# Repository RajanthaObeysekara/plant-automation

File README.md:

# Plant Automation

A cloud-hosted misting/feeding controller for Dendrobium orchid greenhouses
in Sri Lanka. The addressable hardware is **not per-bench** — each farm has
one shared water tank + fertilizer mixing rig, and each greenhouse room has
one shared environment sensor + misting controller. Benches are just named,
positioned spots on a room's floor-plan map. See
[plant-automation-architecture.html](plant-automation-architecture.html)
for the fuller design writeup (some of it predates this room/farm-level
model — the tables below are current).

**New to this repo, or picking it up on a different machine?** Start with
[PROJECT.md](PROJECT.md) for setup and hardware background, but note it
also predates the room/farm re-architecture described here.

## The device model

| Level | What it owns | Addressable? |
|---|---|---|
| **Farm** (🏡) | One shared water tank (low/full sensors) + one fertigation rig (mix → stir → filter → dose). Services whichever room's feed day it is, one room at a time. | Yes — its own `device_key`, polls `/api/device/farm/*` |
| **Room** (🏠, a greenhouse) | One environment sensor (humidity/temp/rain) + misting for every bench in it, together. | Yes — its own `device_key`, polls `/api/device/room/*` |
| **Bench** | A name + a position on the room's map. No sensor, no schedule, no device of its own. | No — plain CRUD via `/api/benches` |

## Parts of this repo

| Path | What it is |
|---|---|
| `backend/` | Node/Express + Postgres + Socket.IO API. Two device-facing route groups (`/api/device/room`, `/api/device/farm`), plus REST + WebSocket for the web app. |
| `frontend/` | React dashboard — farms/rooms, live status, schedules, variety templates, draggable bench floor-plan, history. |
| `simulator/` | A single Node process that plays every room + farm controller in the fleet as live simulated hardware (mist/fertigation/tank state machines), for testing without real hardware. Sensor baselines track real current weather per farm. |
| `firmware/esp32-unit/` | Real ESP32 firmware reference — written for the older per-bench protocol; not yet updated for the room/farm split. |
| `db/init.sql` | Schema, applied automatically on first Postgres start. |

## Run it locally

```bash
cp .env.example .env      # edit if you want different local credentials
docker compose up -d --build
```

- Web app: http://localhost:8090 (default login `admin@example.com` /
  `changeme`, from `.env` — change it before this goes anywhere near
  Railway)
- Backend API directly: http://localhost:4000
- The `simulator` service auto-discovers every farm/room in the database and
  starts polling within seconds — no hardware required to see the whole
  system working.

## Protocols, on purpose

- **Device ↔ backend**: plain REST over HTTP(S), polled on an interval,
  bearer device-key auth (one key per room, one per farm). No broker to
  run, resilient to reconnects — a room keeps misting on its last-synced
  config even if this link is down.
- **Browser ↔ backend**: REST for actions/config, WebSocket (Socket.IO)
  for live push (telemetry, mist/fertigation status) so the dashboard
  doesn't have to poll.
- **User auth**: JWT. **Device auth**: a per-device random key, checked
  with a constant-time comparison against every key on file (cached
  in-memory, refreshed every 20s — see `backend/src/deviceAuth.js`).

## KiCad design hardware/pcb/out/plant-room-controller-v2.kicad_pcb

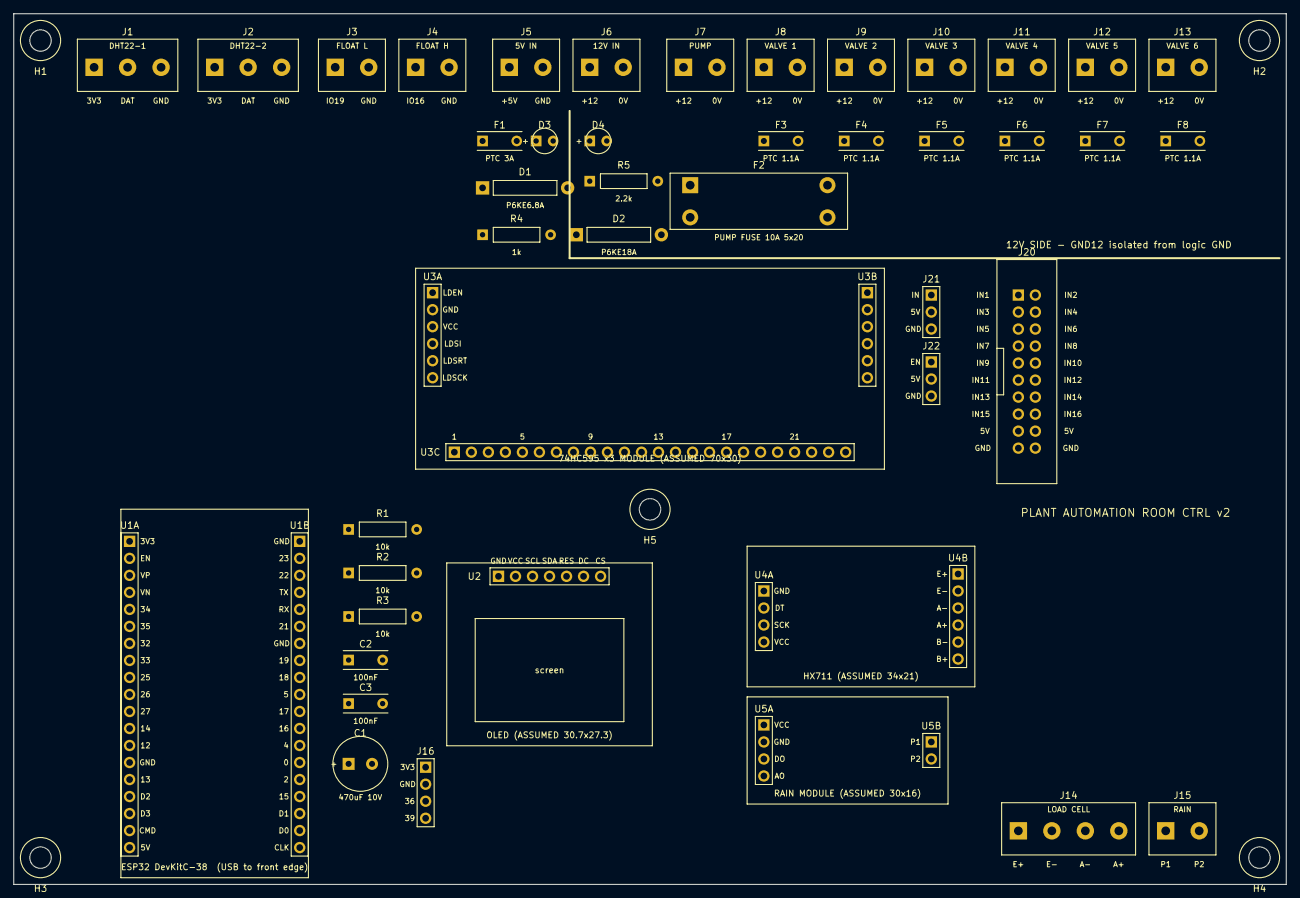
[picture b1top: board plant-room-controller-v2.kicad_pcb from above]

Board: 2 copper layers, 190.0 x 130.0 mm, 54 parts (0 on the bottom side), 58 nets, no tracks yet.

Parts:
C1: 470uF 10V; CP_Radial_D8.0mm_P3.50mm
C2, C3: 100nF; C_Disc_P5.08mm
D1: P6KE6.8A; D_DO-15_P12.70mm
D2: P6KE18A; D_DO-15_P12.70mm
D3: LED 5V; LED_D3.0mm
D4: LED 12V; LED_D3.0mm
F1: PTC 3A; Fuse_PTC_Radial_P5.10mm
F2: PUMP FUSE 10A 5x20; Fuseholder_Clip-5x20mm_P20.50x4.80mm
F3, F4, F5, F6, F7, F8: PTC 1.1A; Fuse_PTC_Radial_P5.10mm
H1, H2, H3, H4, H5: M3; MountingHole_3.2mm_M3
J1: DHT22-1; TerminalBlock_1x03_P5.00mm
J2: DHT22-2; TerminalBlock_1x03_P5.00mm
J3: FLOAT L; TerminalBlock_1x02_P5.00mm
J4: FLOAT H; TerminalBlock_1x02_P5.00mm
J5: 5V IN; TerminalBlock_1x02_P5.00mm
J6: 12V IN; TerminalBlock_1x02_P5.00mm
J7: PUMP; TerminalBlock_1x02_P5.00mm
J8: VALVE 1; TerminalBlock_1x02_P5.00mm
J9: VALVE 2; TerminalBlock_1x02_P5.00mm
J10: VALVE 3; TerminalBlock_1x02_P5.00mm
J11: VALVE 4; TerminalBlock_1x02_P5.00mm
J12: VALVE 5; TerminalBlock_1x02_P5.00mm
J13: VALVE 6; TerminalBlock_1x02_P5.00mm
J14: LOAD CELL; TerminalBlock_1x04_P5.00mm
J15: RAIN; TerminalBlock_1x02_P5.00mm
J16: SPARE IN; PinHeader_1x04_P2.54mm
J20: RELAY BOARD 2x10; IDC_BoxHeader_2x10_P2.54mm
J21: RELAY 17; PinHeader_1x03_P2.54mm
J22: RELAY PWR EN; PinHeader_1x03_P2.54mm
R1, R2, R3: 10k; R_Axial_P10.16mm
R4: 1k; R_Axial_P10.16mm
R5: 2.2k; R_Axial_P10.16mm
U1A, U1B: ESP32 socket 1x19; PinSocket_1x19_P2.54mm
U2: OLED DM0054; PinSocket_1x07_P2.54mm
U3A: 595 IN; PinSocket_1x06_P2.54mm
U3B: 595 CASCADE (NC); PinSocket_1x06_P2.54mm
U3C: 595 OUTPUTS (1-17 USED); PinSocket_1x24_P2.54mm
U4A: HX711 LOGIC; PinSocket_1x04_P2.54mm
U4B: HX711 BRIDGE; PinSocket_1x06_P2.54mm
U5A: RAIN LOGIC; PinSocket_1x04_P2.54mm
U5B: RAIN PLATE; PinSocket_1x02_P2.54mm

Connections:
5V_IN: F1.1, J5.1
+3V3: C2.1, J1.1, J2.1, J16.1, R1.2, R2.2, R3.2, U1A.1, U2.2, U3A.3, U4A.4, U5A.1
+5V: C1.1, C3.1, D1.1, D3.1, F1.2, J20.17, J20.18, J21.2, J22.2, U1A.19
+12V: D2.1, D4.1, F2.1, F2.2, F3.1, F4.1, F5.1, F6.1, F7.1, F8.1, J6.1
DHT1_DATA: J1.2, R1.1, U1B.13
DHT2_DATA: J2.2, R2.1, U1B.6
FLOAT_HIGH: J4.1, U1B.12
FLOAT_LOW: J3.1, U1B.8
GND: C1.2, C2.2, C3.2, D1.2, J1.3, J2.3, J3.2, J4.2, J5.2, J16.2, J20.19, J20.20, J21.3, J22.3, R4.2, U1A.14, U1B.1, U1B.7, U2.1, U3A.2, U4A.1, U5A.2
GND12: D2.2, J6.2, J7.2, J8.2, J9.2, J10.2, J11.2, J12.2, J13.2, R5.2
HX_DT: U1A.6, U4A.2
HX_SCK: U1A.15, U4A.3
LC_AM: J14.3, U4B.3
LC_AP: J14.4, U4B.4
LC_EM: J14.2, U4B.2
LC_EP: J14.1, U4B.1
LED5_K: D3.2, R4.1
LED12_K: D4.2, R5.1
OLED_CS: U1A.11, U2.7
OLED_DC: U1A.12, U2.6
OLED_MOSI: U1B.2, U2.4
OLED_RST: U1A.8, U2.5
OLED_SCLK: U1B.9, U2.3
PUMP_12V: F2.3, F2.4, J7.1
RAIN_AO: U1A.5, U5A.4
RAIN_DO: U1B.11, U5A.3
RAIN_P1: J15.1, U5B.1
RAIN_P2: J15.2, U5B.2
RELAY_PWR_EN: J22.1, U1B.15
RLY_IN1: J20.1, U3C.1
RLY_IN2: J20.2, U3C.2
RLY_IN3: J20.3, U3C.3
RLY_IN4: J20.4, U3C.4
RLY_IN5: J20.5, U3C.5
RLY_IN6: J20.6, U3C.6
RLY_IN7: J20.7, U3C.7
RLY_IN8: J20.8, U3C.8
RLY_IN9: J20.9, U3C.9
RLY_IN10: J20.10, U3C.10
RLY_IN11: J20.11, U3C.11
RLY_IN12: J20.12, U3C.12
RLY_IN13: J20.13, U3C.13
RLY_IN14: J20.14, U3C.14
RLY_IN15: J20.15, U3C.15
RLY_IN16: J20.16, U3C.16
RLY_IN17: J21.1, U3C.17
SPARE_IO36: J16.3, U1A.3
SPARE_IO39: J16.4, U1A.4
SR_CLK: U1B.3, U3A.6
SR_DATA: U1A.7, U3A.4
SR_EN: R3.1, U1A.10, U3A.1
SR_LATCH: U1A.9, U3A.5
V1_12V: F3.2, J8.1
V2_12V: F4.2, J9.1
V3_12V: F5.2, J10.1
V4_12V: F6.2, J11.1
V5_12V: F7.2, J12.1
V6_12V: F8.2, J13.1

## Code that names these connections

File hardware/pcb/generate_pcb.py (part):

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SRX, SRY = 60.0, 38.0
fps.append(row("U3A", "595 IN", SRX + 2.54, SRY + 3.65,
               [("LDEN", "SR_EN"), ("GND", "GND"), ("VCC", "+3V3"), ("LDSI", "SR_DATA"),
                ("LDSRT", "SR_LATCH"), ("LDSCK", "SR_CLK")], labels_side=1))
fps.append(row("U3B", "595 CASCADE (NC)", SRX + 67.46, SRY + 3.65, [("", None)] * 6))
# The module has 24 outputs (3 chips); only Q0-Q16 are used - pins 18-24
# of this socket are mechanical only (no net).
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# ---- Relay ribbon header ----
fps.append(idc_2x10("J20", 150.0, 42.0))
# Relay 17: a separate single-relay module (IN / VCC / GND), next to the ribbon header.
fps.append(row("J21", "RELAY 17", 137.0, 42.0, [("IN", "RLY_IN17"), ("5V", "+5V"), ("GND", "GND")], labels_side=-1, kind="PinHeader"))
# Master relay-coil power enable: GPIO2 (LOW at boot) -> a HIGH-level-trigger
# single relay module whose NO contact feeds the relay board's JD-VCC (jumper
# removed). No relay can energize until the firmware switches this on.
fps.append(row("J22", "RELAY PWR EN", 137.0, 52.0, [("EN", "RELAY_PWR_EN"), ("5V", "+5V"), ("GND", "GND")], labels_side=-1, kind="PinHeader"))

# ---- HX711 module: body 109.5..143.5 x 79.5..100.5 ----
fps.append(row("U4A", "HX711 LOGIC", 112.0, 86.19,
               [("GND", "GND"), ("DT", "HX_DT"), ("SCK", "HX_SCK"), ("VCC", "+3V3")], labels_side=1))
fps.append(row("U4B", "HX711 BRIDGE", 141.0, 83.65,
               [("E+", "LC_EP"), ("E-", "LC_EM"), ("A-", "LC_AM"), ("A+", "LC_AP"), ("B-", None), ("B+", None)], labels_side=-1))
outlines.append((109.5, 79.5, 143.5, 100.5, "HX711 (ASSUMED 34x21)"))

# ---- Rain module: body 109.5..139.5 x 102..118 ----
fps.append(row("U5A", "RAIN LOGIC", 112.0, 106.19,
               [("VCC", "+3V3"), ("GND", "GND"), ("DO", "RAIN_DO"), ("AO", "RAIN_AO")], labels_side=1))
fps.append(row("U5B", "RAIN PLATE", 137.0, 108.73, [("P1", "RAIN_P1"), ("P2", "RAIN_P2")], labels_side=-1))
outlines.append((109.5, 102.0, 139.5, 118.0, "RAIN MODULE (ASSUMED 30x16)"))

# ---- Screw terminals: back edge row (field wiring + power) ----
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# front edge: load cell + rain plate
fps.append(terminal("J14", "LOAD CELL", 150, BH - 8, [("E+", "LC_EP"), ("E-", "LC_EM"), ("A-", "LC_AM"), ("A+", "LC_AP")]))
fps.append(terminal("J15", "RAIN", 172, BH - 8, [("P1", "RAIN_P1"), ("P2", "RAIN_P2")]))
fps.append(row("J16", "SPARE IN", 61.5, 112.5, [("3V3", "+3V3"), ("GND", "GND"), ("36", "SPARE_IO36"), ("39", "SPARE_IO39")], labels_side=-1, kind="PinHeader"))

# ---- Power protection, indicators, fuses ----
fps += [
    two_pin("F1", "PTC 3A", 70, 19, 5.1, "5V_IN", "+5V", "Fuse_PTC_Radial_P5.10mm", drill=0.9),
    two_pin("D3", "LED 5V", 78, 19, 2.54, "+5V", "LED5_K", "LED_D3.0mm", body="led", label=False),
    two_pin("R4", "1k", 70, 33, 10.16, "LED5_K", "GND", "R_Axial_P10.16mm", body="axial"),
    two_pin("D1", "P6KE6.8A", 70, 26, 12.7, "+5V", "GND", "D_DO-15_P12.70mm", drill=1.0, size=2.0, body="axial"),
    two_pin("D4", "LED 12V", 86, 19, 2.54, "+12V", "LED12_K", "LED_D3.0mm", body="led", label=False),
    two_pin("R5", "2.2k", 86, 25, 10.16, "LED12_K", "GND12", "R_Axial_P10.16mm", body="axial"),
    two_pin("D2", "P6KE18A", 84, 33, 12.7, "+12V", "GND12", "D_DO-15_P12.70mm", drill=1.0, size=2.0, body="axial"),
    fuse_clips("F2", "PUMP FUSE 10A 5x20", 101, 28, "+12V", "PUMP_12V"),
]
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
# ---- Pull-ups and decoupling (next to the ESP32) ----
fps += [
    two_pin("R1", "10k", 50, 77, 10.16, "DHT1_DATA", "+3V3", "R_Axial_P10.16mm", body="axial"),
    two_pin("R2", "10k", 50, 83.5, 10.16, "DHT2_DATA", "+3V3", "R_Axial_P10.16mm", body="axial"),
    two_pin("R3", "10k", 50, 90, 10.16, "SR_EN", "+3V3", "R_Axial_P10.16mm", body="axial"),
    two_pin("C2", "100nF", 50, 96.5, 5.08, "+3V3", "GND", "C_Disc_P5.08mm"),
    two_pin("C3", "100nF", 50, 103, 5.08, "+5V", "GND", "C_Disc_P5.08mm"),
    two_pin("C1", "470uF 10V", 50, 112, 3.5, "+5V", "GND", "CP_Radial_D8.0mm_P3.50mm", drill=0.9, size=1.8, body="radial"),
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
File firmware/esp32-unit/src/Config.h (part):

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// left unconnected. A 10k resistor from LDEN to 3V3 keeps every output
// disabled while the ESP32 boots, until ShiftRegister::begin() has latched
// an all-off frame — so no relay can click on at power-up.
#define PIN_SR_DATA   32 // LDSI  (SER)
#define PIN_SR_CLOCK  22 // LDSCK (SRCLK)
#define PIN_SR_LATCH  25 // LDSRT (RCLK)
#define PIN_SR_ENABLE 26 // LDEN  (OE) + 10k pull-up to 3V3
#define SR_ENABLE_ACTIVE_LOW true // standard 74HC595 OE; flip if outputs never switch
#define SR_CHIP_COUNT 3
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// 3-pin hardware-SPI one.
#define OLED_WIDTH 96
#define OLED_HEIGHT 64
#define PIN_OLED_CS   27
#define PIN_OLED_DC   14
#define PIN_OLED_MOSI 23
#define PIN_OLED_SCLK 18
#define PIN_OLED_RST  33

// ---------- Timing ----------
// Local sensor read + telemetry-send-check cadence. Reading is free (no
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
